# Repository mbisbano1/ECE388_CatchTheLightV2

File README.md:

# ECE388_CatchTheLightV2
Michael Bisbano's Fall 2020 ECE 388 Project: CatchTheLightV2

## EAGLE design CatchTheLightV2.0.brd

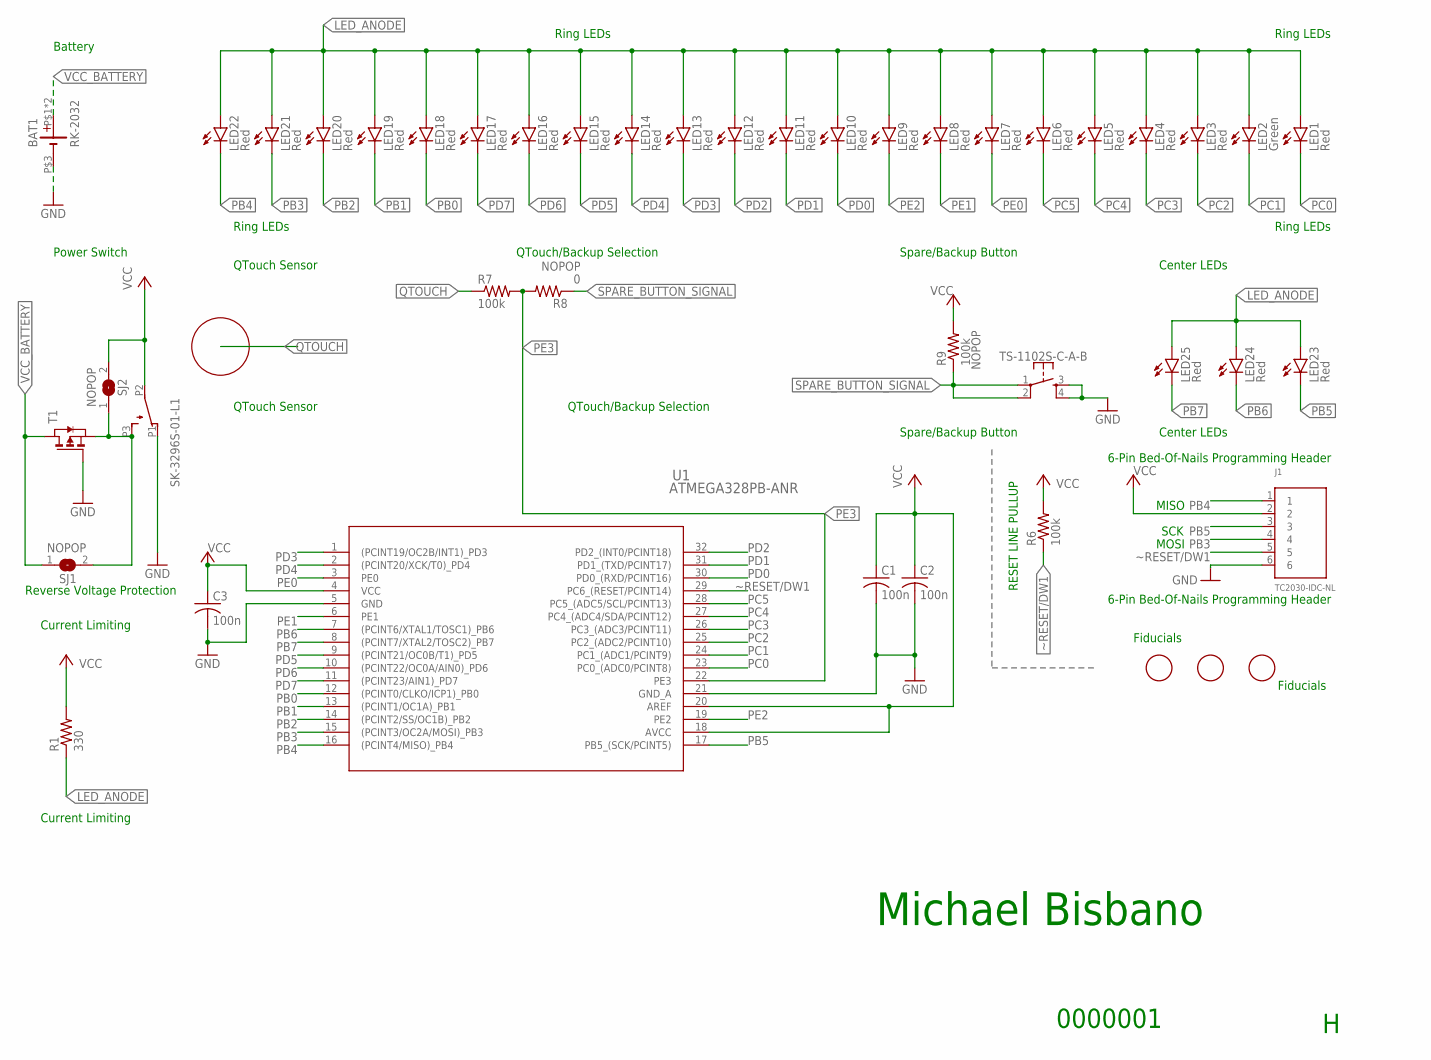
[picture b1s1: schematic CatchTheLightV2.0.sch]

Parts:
BAT1: RK-2032
C1, C2, C3: 100n; CAPC2012X110
J1: TC2030-IDC-NL; TAG_TC2030-IDC-NL
LED1, LED3, LED4, LED5, LED6, LED7, LED8, LED9, LED10, LED11, LED12, LED13, LED14, LED15, LED16, LED17, LED18, LED19, LED20, LED21, LED22, LED23, LED24: Red; CHIP-LED0805
LED2: Green; CHIP-LED0805
LED25: Red; CHIPLED_0805
PB1: SK-3296S-01-L1
PB2: PB2; TS-1102S-C-A-B
R1: 330; R0805
R6, R7, R9: 100k; R0805
R8: 0; R0805
SJ1, SJ2: NOPOP; SJW
T1: PMOSSOT23; SOT-23
U1: ATMEGA328PB-ANR; 32A_MCH
U$4, U$5, U$6: FIDUCIAL; FIDUCIAL_1MM

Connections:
GND: BAT1.P$3 (-), C1.2, C2.2, C3.2, J1.6, PB1.P1 (1), PB2.3, PB2.4, T1.3 (G), U1.5 (GND), U1.21 (GND_A)
LED_ANODE: LED1.A, LED2.A, LED3.A, LED4.A, LED5.A, LED6.A, LED7.A, LED8.A, LED9.A, LED10.A, LED11.A, LED12.A, LED13.A, LED14.A, LED15.A, LED16.A, LED17.A, LED18.A, LED19.A, LED20.A, LED21.A, LED22.A, LED23.A, LED24.A, LED25.A, R1.1
PB0: LED18.C, U1.12 ((PCINT0/CLKO/ICP1)_PB0)
PB1: LED19.C, U1.13 ((PCINT1/OC1A)_PB1)
PB2: LED20.C, U1.14 ((PCINT2/SS/OC1B)_PB2)
PB3: J1.4, LED21.C, U1.15 ((PCINT3/OC2A/MOSI)_PB3)
PB4: J1.1, LED22.C, U1.16 ((PCINT4/MISO)_PB4)
PB5: J1.3, LED23.C, U1.17 (PB5_(SCK/PCINT5))
PB6: LED24.C, U1.7 ((PCINT6/XTAL1/TOSC1)_PB6)
PB7: LED25.C, U1.8 ((PCINT7/XTAL2/TOSC2)_PB7)
PC0: LED1.C, U1.23 (PC0_(ADC0/PCINT8))
PC1: LED2.C, U1.24 (PC1_(ADC1/PCINT9))
PC2: LED3.C, U1.25 (PC2_(ADC2/PCINT10))
PC3: LED4.C, U1.26 (PC3_(ADC3/PCINT11))
PC4: LED5.C, U1.27 (PC4_(ADC4/SDA/PCINT12))
PC5: LED6.C, U1.28 (PC5_(ADC5/SCL/PCINT13))
PD0: LED10.C, U1.30 (PD0_(RXD/PCINT16))
PD1: LED11.C, U1.31 (PD1_(TXD/PCINT17))
PD2: LED12.C, U1.32 (PD2_(INT0/PCINT18))
PD3: LED13.C, U1.1 ((PCINT19/OC2B/INT1)_PD3)
PD4: LED14.C, U1.2 ((PCINT20/XCK/T0)_PD4)
PD5: LED15.C, U1.9 ((PCINT21/OC0B/T1)_PD5)
PD6: LED16.C, U1.10 ((PCINT22/OC0A/AIN0)_PD6)
PD7: LED17.C, U1.11 ((PCINT23/AIN1)_PD7)
PE0: LED7.C, U1.3 (PE0)
PE1: LED8.C, U1.6 (PE1)
PE2: LED9.C, U1.19 (PE2)
PE3: R7.2, R8.2, U1.22 (PE3)
PROTECTED_VBAT: PB1.P3 (3), SJ1.2, SJ2.1, T1.2 (S)
QTOUCH: R7.1
SPARE_BUTTON_SIGNAL: PB2.1, PB2.2, R8.1, R9.1
VCC: C1.1, C2.1, C3.1, J1.2, PB1.P2 (2), R1.2, R6.2, R9.2, SJ2.2, U1.4 (VCC), U1.18 (AVCC), U1.20 (AREF)
VCC_BATTERY: BAT1.P$1 (+), BAT1.P$2 (+), SJ1.1, T1.1 (D)
~RESET/DW1: J1.5, R6.1, U1.29 (PC6_(RESET/PCINT14))

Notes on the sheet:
0000001
Current Limiting
Battery
RESET LINE PULLUP
Ring LEDs
Center LEDs
Spare/Backup Button
QTouch/Backup Selection
QTouch Sensor
6-Pin Bed-Of-Nails Programming Header
Power Switch
Reverse Voltage Protection
Michael Bisbano
Fiducials
SCK
MOSI
MISO

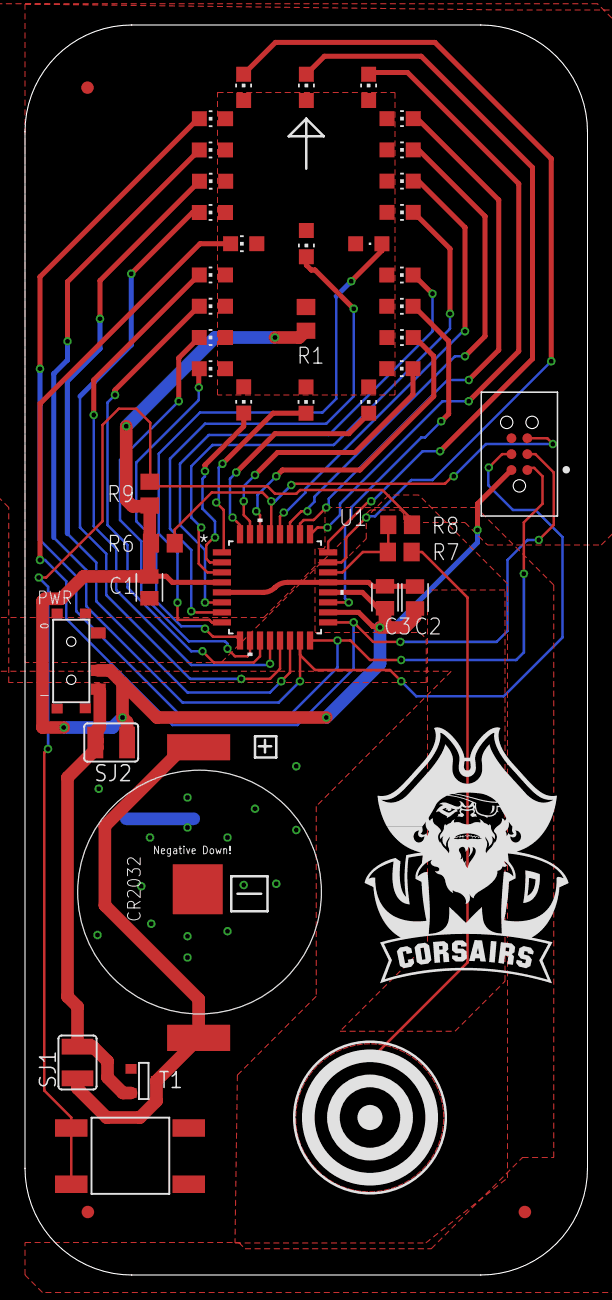
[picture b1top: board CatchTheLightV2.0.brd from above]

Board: 2 copper layers, 45.0 x 100.0 mm, 44 parts (0 on the bottom side), 33 nets.

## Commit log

2020-10-12 First Commit of files
    Added base version of software, and unfinished schematic
2020-10-12 Fixed BOM
    BOM was reformatted to meet expectations.
2020-10-14 Revised BOM
    Added Tolerances and Rating column in for passives
2020-10-14 Delete CatchTheLightV2.0.s#1
    this is in the .gitignore
2020-10-14 Delete CatchTheLightV2.0.s#2
    in .gitignore
2020-10-14 Delete CatchTheLightV2.0.s#3
    in .gitignore
2020-10-14 Delete CatchTheLightV2.0.xlsx
    xlsx file not needed for submission, .csv file is saved instead
2020-10-14 Delete FormalBom1.xlsx
    backup of old BOM, not needed for submission
2020-10-15 Update CatchTheLightV2.0.sch
    modified Schematic to add features
2020-10-16 Update CatchTheLightV2.0.sch
    Created CustomParts.lbr for backup push button and power switch components, implemented them into schematic.
2020-10-16 Added Eagle Libraries Folder
    Added folder of eagle libraries for making things easier
2020-10-16 Replaced Old Switch and Button components
    New Library components added, in process of modifying bom
2020-10-17 Finalized BOM
    New values and components included
2020-10-17 Updated Battery Holder
    Battery holder updated in schematic, Custom Parts Library, and in BOM. Price not included in BOM for Battery holder as we cannot find it online
2020-10-19 Final fixes to BOM
    Final fixes to BOM made.
    Also started laying out board.
2020-10-22 Began Writing 7seg code
2020-10-23 Finished development of 7Seg LED test code
2020-11-03 Revised Schematic and Board design to use correct 328pb footprint
    Modified a whole lot. New approach to board design. Will try to fill in all wiring first, and then draw in the rest of the pours/planes
2020-11-03 Finished Routing V1
    Routing finished, no gnd planes yet
2020-11-06 Schematic pdf updated and put in renders
2020-11-06 Annoying libraries get out of my face
2020-11-06 Board V1
    First crack at board. Nervous about trace width for dissipating too much power. Also VERY unsure of qtouch button layout and traces.. We will see, will likely be modifying as the week goes on.
2020-11-09 Schematic Submission Issues addressed
    Changes documented in issue
2020-11-09 whoops forgot pdf of schematic
2020-11-09 Board Updated to meet some issue requirements
    Fiducials relocated according to spec
    Silkscreen labels updated
    Silkscreen over battery pads removed. Thermal Relief restored on GND pad.
2020-11-10 Removed Programming line resistors
    Removed programming line resistors and renamed plug of nails to bed of nails.
2020-11-11 PMOS Reverse Protection in Schematic and Board
    Swapped in PMOS over Schottky diode for reverse protection
2020-11-11 Gerber Files Updated with Board design
2020-11-11 Slight Changes/Optimizations on board
2020-11-11 Moved switch in from edge of board for more clearance
2020-11-11 Revised to fix issues
    Silk screen removed from top of pads for Switch and for Battery holder
2020-11-11 Silk Screen Modified
    Silk Screen Modified, Should be last edit necessary.
2020-11-12 UMD Logo Added
    Snazzy
2020-11-20 Added Assembly CSV
    Assembly CSV is available. Located in root, titled CatchTheLightV2_assembly.csv
2020-12-03 Code Working, still ironing out tiny bugs
    Working Code
    Also submitting photos and videos of board working
2020-12-05 Green Light Hold Bug Fix
    Green Light Hold fixed:
    - Removed offending delayScaler++ from within X code in ISR.
2020-12-06 Added features
    - Increase speed when correct
    - Direction tricking (switch directions randomly)..
    - Fancy animations
2020-12-08 Added ReportScore Test settings
2020-12-14 Random Code Changes

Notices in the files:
parts and their libraries:
COPYRIGHT: Copyright (C) 2018 Accelerated Designs. All rights reserved
